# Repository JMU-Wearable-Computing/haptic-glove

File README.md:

# haptic-glove

## Haptic Effect Waveforms

[Image source](https://learn.adafruit.com/assets/72593)

## PCB (Printed Circuit Board)

### Schematic V2.1

### Layout V2.1

#### PCB Edit History
##### V2.0
- Initial board redesign
##### V2.1
- Shifted Arduino placement down 1 mm to allow for more clearance between the Arduino and the motor header pins
- Added graphic to denote onboard IMU directions
- Added a spot on the back of the board to write the board's device ID
- Shifted some silkscreen placements so that part names are not cut off by pads
- Added text to denote correct Arduino orientation
  
## Eagle PCB Set-Up

### OSHPark Plugin
The OSHPark Eagle plugin includes OSHPark design rules and allows the user to send the .brd file directly to an OSHPark cart. See the [OSHPark-Eagle-Tools GitHub](https://github.com/OSHPark/OSHPark-Eagle-Tools)

### Libraries
Included in the repository are:
1. TCA9548APWR.lbr (I2C multiplexer)
2. SparkFun-Eagle-Libraries-main.zip

## Arduino Nano Arduino IDE setup 

### Correct IDE version
Arduino IDE 2.X.X

### Correct board library and name:
#### Board Library
Arduino SAMD Boards (32-bits ARM Cortex-M0+)

#### Board Name
Arduino NANO 33 IoT

### Arduino Libraries
 
1. Adafruit_DRV2605.h
2. Arduino_LSM6DS3.h
3. WiFiNINA.h

### Troubleshooting
Sometimes, Arduino IDE fails to recognize that Nano 33 IoT is connected to a USB port. Should this happen, try the following fixes:
- Attempt to connect it to other USB ports on your machine
- If the above does not work, quickly double click the `RST` button on the Arduino while it is plugged into your machine. This will cause your Arduino's bootloader to run indefinitely. You will know that it has entered this state when you see the onboard LED slowly pulsing on and off. Arduino IDE should now recognize it and you should now be able to upload code.

If neither of these options work, then it is likely that either

(A). the bootloader on the Arduino is missing or corrupted, or  
(B). there is some hardware damage on the Arduino.

Sources: [Forum post 1](https://forum.arduino.cc/t/solved-arduino-nano-33-iot-not-recognized-by-windows-10/621376) & [Forum post 2](https://forum.arduino.cc/t/arduino-nano-33-iot-not-recognized-by-pc/1192703/4)

## Communicating with Nano 33 IoT

Nano 33 IoT can be communicated with via TCP socket connection.
Network credentials can be modified with the `ssid` and `password` variables within the Arduino code.
When booted, the Nano 33 IoT establishes a user definable static IP.

### Onboard LED state meanings
|State|Meaning|
--- | --- |
|OFF|Not connected to network|
|ON|Connected to user specified network|

### Message format
Messages follows the format: `X,n01,n02,n03,n04,n05,n06,n07,n08`

**NOTE FOR SERIAL COMMUNICATION ONLY:** Despite the known issue with [the dastardly eighth motor driver](#the-dastardly-eighth-motor-driver), the message format remains the same. Even if you are not using all eight drivers in your application with Serial communication, values for all eight drivers should be passed if you are sending an [effect message](#effect-messages) unless you are sending an [all stop message](#all-stop-message).

X is a char that signifies the message type. nXX is a number.
Negative numbers will be ignored and the playback of the current haptic effect will continue.
0 will stop the corresponding driver.
All decimals will be rounded DOWN.
Each segment of the message correspondes to the strength of a specific haptic driver, where n01 controls driver 1, n02 controls driver 2, and so on.

#### Effect Messages
For messages of type 'E', numbers [1, 123] will set the playback effect of the corresponding driver.
Numbers higher than 123 will set the playback effect to effect # 123.

##### All Stop Message
Should you want to halt the haptic playback of all drivers, simply passing `'E'` as the entire effect message will do this.

##### Example
The message `'E',100,43,55,1,123,34,99,2` will cause driver one to activate using haptic effect # 100, driver two to activate using haptic effect # 43, and so on. Passing the message `'E',0,-1,100.7,9999,0,0,0,0` afterwards will stop drivers 1, 5, 6, 7, and 8. Driver 2 will remain activated with the same haptic effect as before (# 43), driver 3 will activate using haptic effect # 100, and driver 4 will activate using haptic effect # 123.

#### Acceleration Messages
For messages of type 'A', numbers are used to toggle the continuous collection of acceleration data. Only one number should be passed. Passing the number zero will halt data collection, while any other number will resume data collection. For simplicity's sake, it is recommended to only use the number one to resume data collection. Once started, data will be continuously returned and sent to the client until another acceleration message is recieved that instructs the system to halt data collection.

##### Example
The message `'A',1` will begin continuous acceleration data collection and sending. The message `'A',0` will halt all acceleration data collection and sending.

## Tutorials
### Arduino IDE setup
This will teach you how to set up the Arduino IDE for use of the haptic glove. Prior to following this tutorial, you should already have the Arduino IDE downloaded.

1. Open `firmware-V2.ino`. `network_cred.h` should automatically open in a separate tab
2. Click the `network_cred.h` tab at the top and input your WiFi credentials. Press <kbd>Command</kbd> + <kbd>S</kbd> to save your edits on a Mac (<kbd>Control</kbd> + <kbd>S</kbd> on Windows).
3. Open the Boards Manager by clicking the correct icon on the left of the IDE. Search for `nano 33 iot`. The one board library that should be shown is `Arduino SAMD Boards (32-bits ARM Cortex-M0+)`. Install this library. Feel free to install a newer version than what is shown in the picture.

4. Open the Library manager by clicking the correct icon on the left of the IDE. Search for and install `Adafruit DRV2605 Library`, `Arduino_LSM6DS3` and `WiFiNINA`. Feel free to install newer versions than what are shown in the pictures.

5. Navigate to `Tools`>`Board`>`Arduino`>`SAMD Boards (32-bits ARM Cortex-M0+)` and select `Arduino Nano 33 IoT` as the board.
6. Congratulations! Arduino IDE is now set up to be used with the haptic glove.

### Communicating with the Arduino via serial port
This will teach you how to send messages to the Arduino via the Serial port that will control the haptic motor drivers and the onboard IMU.

#### Initial Arduino set up
1. Complete the [Arduino IDE setup tutorial](#arduino-ide-setup).
2. Set the user-definable variables in the firmware. The value of the variable `DEVICE_ID` does not matter when using serial communication.

**NOTE:** See the [Known Issues section](#known-issues) for an explanation of `theDastardlyEighthDriver`

3. Ensure that the Serial Monitor baud rate is set to 9600

4. Connect the Arduino to your computer via USB, ensure the correct board and port are selected in the Arduino IDE, and upload the firmware by clicking the arrow button in the top left of the IDE.

#### Example Use
We will use an example message that was used in the [Message Format section](#message-format). Feel free to use other example messages from that section to familiarize yourself with the message structure. Or, be brave and create your own message (just be sure to follow the correct structure!)

##### Turning all drivers on with an effect message
1. In the serial monitor, type the following message and then press <kbd>Enter</kbd> (enter it EXACTLY as it appears here): `E,100,43,55,1,123,34,99,2`

2. If the variable `debug` is set to `true`, the following should be the last of what prints to the Serial Monitor:

3. All drivers should now be activated. Driver number 1 should be set to haptic effect # 100, driver number 2 should be set to haptic effect # 43, and so on.

##### Accessing the accelerometer data using an acceleration message
1. In the serial monitor, type the following message and then press <kbd>Enter</kbd> (enter it EXACTLY as it appears here): `A,1`

2. As long as the variable `debug` is set to `true`, the following should print to the Serial Monitor. `outMsg` is the object that is sent to the TCP client. Acceleration data is now being continuously collected.

3. Now input the message `A,0` or just simply `A` into the Serial Monitor. Notice how the continuous collection of accelerometer data has stopped.

### Communicating with the Arduino via TCP socket connection
This will teach you how to send messages to the Arduino via a TCP socket to control the haptic motor drivers and the onboard IMU.

#### Initial Arduino set up
1. Complete the [Arduino IDE setup tutorial](#arduino-ide-setup).
2. Set the user-definable variables in the firmware. Be sure to set `DEVICE_ID` to a unique integer [10, 100].

3. Connect the Arduino to your computer via USB, ensure the correct board and port are selected in the Arduino IDE, and upload the firmware by clicking the arrow button in the top left of the IDE.
4. Once uploaded, you can safely unplug the Arduino from your computer. Congratulations! Your Arduino now has the necessary software and is ready for use with the haptic glove.

#### Setting up Python
This assumes that you already have Python installed and can successfully run a Python script.
1. Clone this repository (glove-V2) to your local computer
2. Open the repository in your preferred IDE (PyCharm is recommended)
3. Congrats! Python is now ready for use with the haptic glove.

#### Example Use
We will use `glove-demo-single.py` for this example. This is meant as a demonstration of the glove-V2 capabilities so that you can go on and create your own applications using the same methods.

1. After cloning this repository, open `glove-demo-single.py`
2. Ensure the correct parameters are set for the Glove object (`device_id`, `port`, `acceleration`, and `verbose`). Explanations for these parameters are in this Python file
3. The demo script is now ready for use. You can go ahead and run it, or customize the effect numbers that are sent to the glove.

**NOTE:** If you choose to activate the accelerometer on the Arduino (this is the default) then be sure that the `acceleration` property of the glove object is set to `True`. This will turn on continuous transmission of acceleration data until the Python script ends. Be sure that `glove.accel_loop` is set to `False` at the end of this example script. Otherwise, the program will be stuck in a loop and will continue to output acceleration data until the program is manually killed.

## Known Issues
### The Dastardly Eighth Motor Driver
#### Explanation and Recommendation
If you are attempting to control the motor drivers via TCP socket connection, attempting to activate the eighth driver (including if you tell it to halt effect playback by passing a zero in the correct place in an [effect message](#effect-messages) when it is already not activated) will cause the WiFi to disconnect. This will prevent reconnection until the onboard WiFi chip is fully turned off/on again by calling `WiFi.end()` and then the custom `WiFiConnect()` function that performs all of the initial WiFi connection procedures. Because of the nature of TCP socket connections, this requires the Arduino and desktop computer to restart their connection and create a new socket and client, at which point the problem will (99 times out of 100) happen again. To remedy this, the boolean variable `theDastardlyEighthDriver` has been added to the firmware that controls the use of the eighth driver. If you are at all using TCP socket connections with the haptic glove, be sure to keep this variable set to `false` so that the WiFi disconnect problem does not occur. You will only be able to use seven of the eight drivers, but the WiFi connection will be reliable and shouldn't drop. If you are strictly using Serial communication to control the motor drivers, then feel free to set `theDastardlyEighthDriver` to `true`. This will allow you to use all eight drivers for your application.
#### Potential Cause
The current theory for why this issue is happening is that the moment the I2C multiplexer begins to communicate with this eighth driver, since the driver's I2C lines are tied high and the mux pulls them low to communicate, power and ground are very briefly shorted. It is believed that this short then messes with the WiFi chip's power supply, causing WiFi to drop and requiring the WiFi chip to be reset.

This issue is present on all of the existing haptic glove V2.0 boards, so it is not believed that it is simply an issue with the soldering of the components, however this is still a possibility. However, it may be a tolerance issue with the traces on the PCB itself. As of now (May 2024), no V2.1 boards have been fabricated so it is unknown if this issue is present on those (although it is likely that it is). Also, it is worth noting that during fabrication of the PCBs there was a power-ground short somewhere that disappeared before we could track down the cause. It disappeared once all components were soldered onto the PCB. This may be related to the problem explained above, although there is no corroborating evidence to prove that this is the case.

The true cause of this issue is unknown, so it is best to utilize the `theDastardlyEighthDriver` variable to only use seven drivers if your application uses TCP sockets.

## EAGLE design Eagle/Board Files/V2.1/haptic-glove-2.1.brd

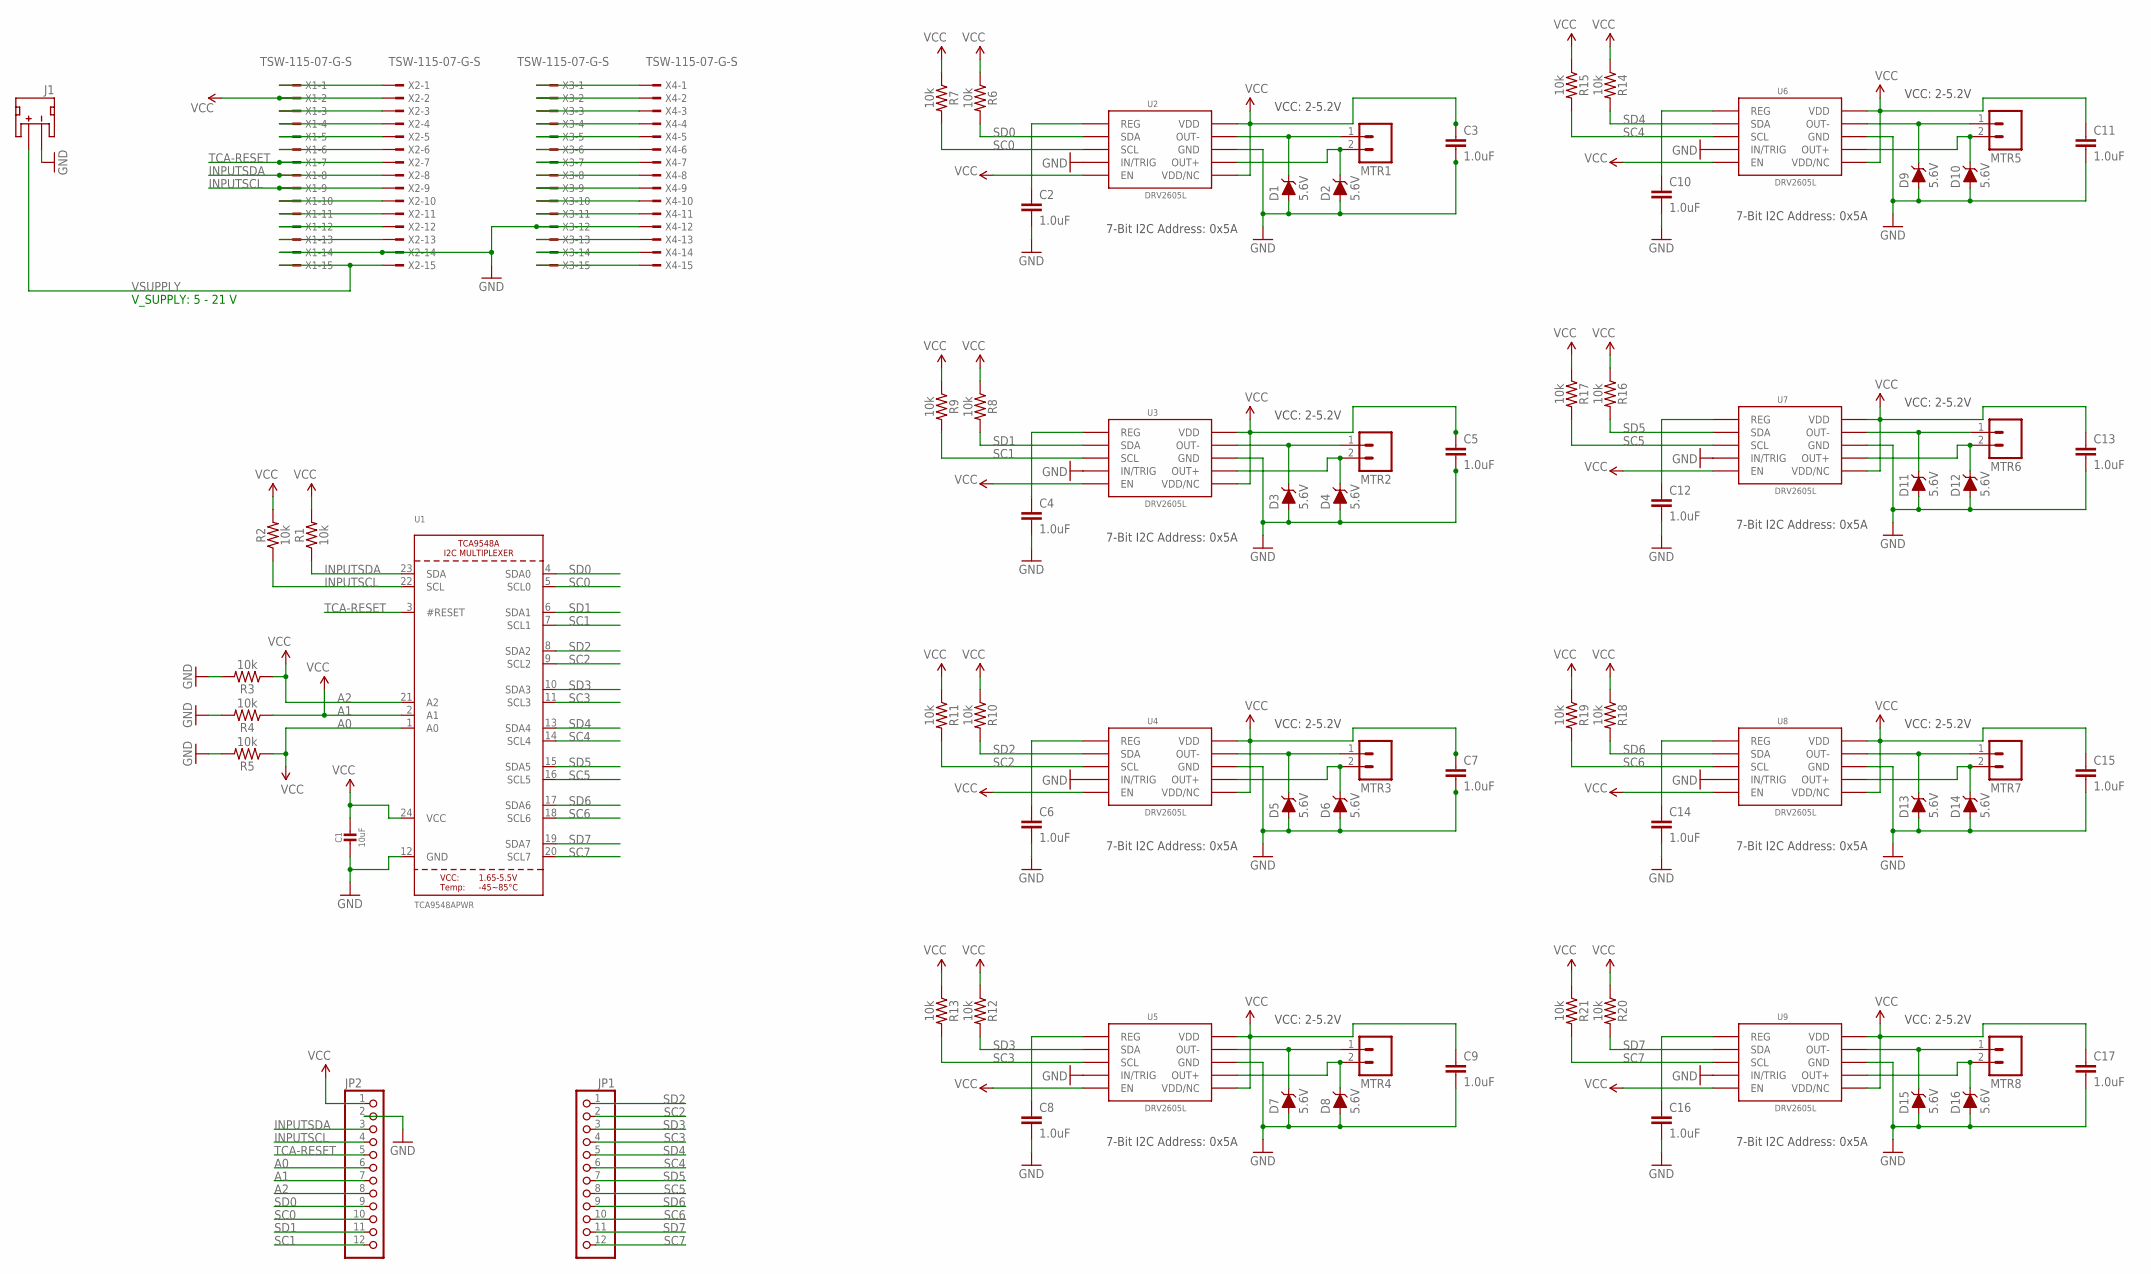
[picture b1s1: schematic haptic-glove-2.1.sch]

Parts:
C1: 10uF; 0805-NO
C2, C3, C4, C5, C6, C7, C8, C9, C10, C11, C12, C13, C14, C15, C16, C17: 1.0uF; 0402-CAP; MPN GRM155R61E105KA12D
D1, D2, D3, D4, D5, D6, D7, D8, D9, D10, D11, D12, D13, D14, D15, D16: 5.6V; SOD-323
J1: JST_2MM_MALE; JST-2-SMD
JP1, JP2: HEADER-1X12; 1X12_ROUND
MTR1, MTR2, MTR3, MTR4, MTR5, MTR6, MTR7, MTR8: M02PTH; 1X02@1
R1, R2, R3, R4, R5, R6, R7, R8, R9, R10, R11, R12, R13, R14, R15, R16, R17, R18, R19, R20, R21: 10k; 0603
U1: TCA9548APWR; TSSOP24
U2, U3, U4, U5, U6, U7, U8, U9: DRV2605L; VSSOP-10
X1, X2, X3, X4: TSW-115-07-G-S; TSW-115-XX-G-S

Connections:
A0: JP2.6, R5.1, U1.1 (A0)
A1: JP2.7, R4.1, U1.2 (A1)
A2: JP2.8, R3.1, U1.21 (A2)
EN1: X3.2, X4.2
EN2: X3.4, X4.4
EN3: X3.8, X4.8
EN4: X3.11, X4.11
GND: C1.2, C2.2, C3.2, C4.2, C5.2, C6.2, C7.2, C8.2, C9.2, C10.2, C11.2, C12.2, C13.2, C14.2, C15.2, C16.2, C17.2, D1.A, D2.A, D3.A, D4.A, D5.A, D6.A, D7.A, D8.A, D9.A, D10.A, D11.A, D12.A, D13.A, D14.A, D15.A, D16.A, J1.1 (-), JP2.2, R3.2, R4.2, R5.2, U1.12 (GND), U2.P$4 (IN/TRIG), U2.P$8 (GND), U3.P$4 (IN/TRIG), U3.P$8 (GND), U4.P$4 (IN/TRIG), U4.P$8 (GND), U5.P$4 (IN/TRIG), U5.P$8 (GND), U6.P$4 (IN/TRIG), U6.P$8 (GND), U7.P$4 (IN/TRIG), U7.P$8 (GND), U8.P$4 (IN/TRIG), U8.P$8 (GND), U9.P$4 (IN/TRIG), U9.P$8 (GND), X1.14, X2.14, X3.12, X4.12
IN/TRIG1: X3.1, X4.1
IN/TRIG2: X3.3, X4.3
IN/TRIG3: X3.7, X4.7
IN/TRIG4: X3.10, X4.10
IN/TRIG5: X1.6, X2.6
INPUTSCL: JP2.4, R2.1, U1.22 (SCL), X1.9, X2.9
INPUTSDA: JP2.3, R1.1, U1.23 (SDA), X1.8, X2.8
unnamed: C4.1, U3.P$1 (REG)
unnamed: C10.1, U6.P$1 (REG)
unnamed: D9.C, MTR5.1, U6.P$9 (OUT-)
unnamed: D3.C, MTR2.1, U3.P$9 (OUT-)
unnamed: D4.C, MTR2.2, U3.P$7 (OUT+)
unnamed: C8.1, U5.P$1 (REG)
unnamed: D10.C, MTR5.2, U6.P$7 (OUT+)
unnamed: X1.1, X2.1
unnamed: D7.C, MTR4.1, U5.P$9 (OUT-)
unnamed: D8.C, MTR4.2, U5.P$7 (OUT+)
unnamed: C6.1, U4.P$1 (REG)
unnamed: X1.3, X2.3
unnamed: D5.C, MTR3.1, U4.P$9 (OUT-)
unnamed: D6.C, MTR3.2, U4.P$7 (OUT+)
unnamed: C12.1, U7.P$1 (REG)
unnamed: X1.4, X2.4
unnamed: D11.C, MTR6.1, U7.P$9 (OUT-)
unnamed: D12.C, MTR6.2, U7.P$7 (OUT+)
unnamed: C14.1, U8.P$1 (REG)
unnamed: X1.5, X2.5
unnamed: D13.C, MTR7.1, U8.P$9 (OUT-)
unnamed: D14.C, MTR7.2, U8.P$7 (OUT+)
unnamed: C16.1, U9.P$1 (REG)
unnamed: D15.C, MTR8.1, U9.P$9 (OUT-)
unnamed: D16.C, MTR8.2, U9.P$7 (OUT+)
unnamed: C2.1, U2.P$1 (REG)
unnamed: X1.10, X2.10
unnamed: X1.11, X2.11
unnamed: D1.C, MTR1.1, U2.P$9 (OUT-)
unnamed: D2.C, MTR1.2, U2.P$7 (OUT+)
unnamed: X1.12, X2.12
unnamed: X1.13, X2.13
unnamed: X3.5, X4.5
unnamed: X3.6, X4.6
unnamed: X3.9, X4.9
unnamed: X3.13, X4.13
unnamed: X3.14, X4.14
unnamed: X3.15, X4.15
SC0: JP2.10, R7.2, U1.5 (SCL0), U2.P$2 (SCL)
SC1: JP2.12, R9.2, U1.7 (SCL1), U3.P$2 (SCL)
SC2: JP1.2, R11.2, U1.9 (SCL2), U4.P$2 (SCL)
SC3: JP1.4, R13.2, U1.11 (SCL3), U5.P$2 (SCL)
SC4: JP1.6, R15.2, U1.14 (SCL4), U6.P$2 (SCL)
SC5: JP1.8, R17.2, U1.16 (SCL5), U7.P$2 (SCL)
SC6: JP1.10, R19.2, U1.18 (SCL6), U8.P$2 (SCL)
SC7: JP1.12, R21.2, U1.20 (SCL7), U9.P$2 (SCL)
SD0: JP2.9, R6.2, U1.4 (SDA0), U2.P$3 (SDA)
SD1: JP2.11, R8.2, U1.6 (SDA1), U3.P$3 (SDA)
SD2: JP1.1, R10.2, U1.8 (SDA2), U4.P$3 (SDA)
SD3: JP1.3, R12.2, U1.10 (SDA3), U5.P$3 (SDA)
SD4: JP1.5, R14.2, U1.13 (SDA4), U6.P$3 (SDA)
SD5: JP1.7, R16.2, U1.15 (SDA5), U7.P$3 (SDA)
SD6: JP1.9, R18.2, U1.17 (SDA6), U8.P$3 (SDA)
SD7: JP1.11, R20.2, U1.19 (SDA7), U9.P$3 (SDA)
TCA-RESET: JP2.5, U1.3 (#RESET), X1.7, X2.7
VCC: C1.1, C3.1, C5.1, C7.1, C9.1, C11.1, C13.1, C15.1, C17.1, JP2.1, R1.2, R2.2, R6.1, R7.1, R8.1, R9.1, R10.1, R11.1, R12.1, R13.1, R14.1, R15.1, R16.1, R17.1, R18.1, R19.1, R20.1, R21.1, U1.24 (VCC), U2.P$5 (EN), U2.P$6 (VDD/NC), U2.P$10 (VDD), U3.P$5 (EN), U3.P$6 (VDD/NC), U3.P$10 (VDD), U4.P$5 (EN), U4.P$6 (VDD/NC), U4.P$10 (VDD), U5.P$5 (EN), U5.P$6 (VDD/NC), U5.P$10 (VDD), U6.P$5 (EN), U6.P$6 (VDD/NC), U6.P$10 (VDD), U7.P$5 (EN), U7.P$6 (VDD/NC), U7.P$10 (VDD), U8.P$5 (EN), U8.P$6 (VDD/NC), U8.P$10 (VDD), U9.P$5 (EN), U9.P$6 (VDD/NC), U9.P$10 (VDD), X1.2, X2.2
VSUPPLY: J1.2 (+), X1.15, X2.15

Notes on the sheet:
7-Bit I2C Address: 0x5A
VCC: 2-5.2V
V_SUPPLY: 5 - 21 V

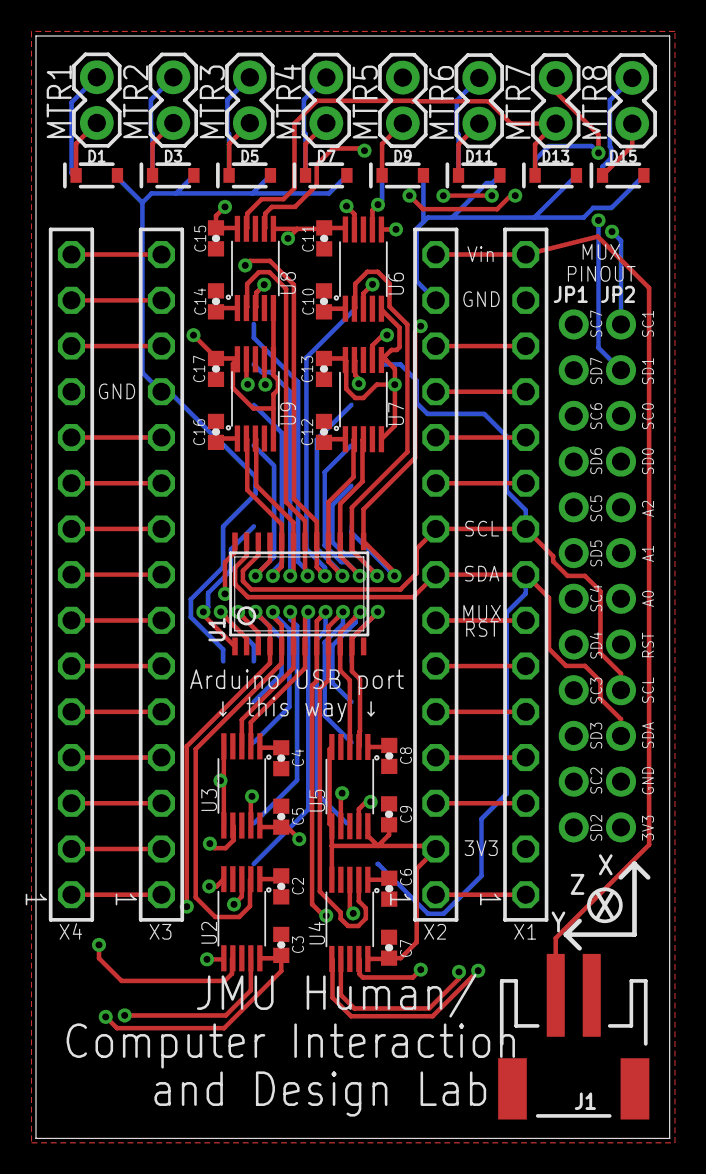
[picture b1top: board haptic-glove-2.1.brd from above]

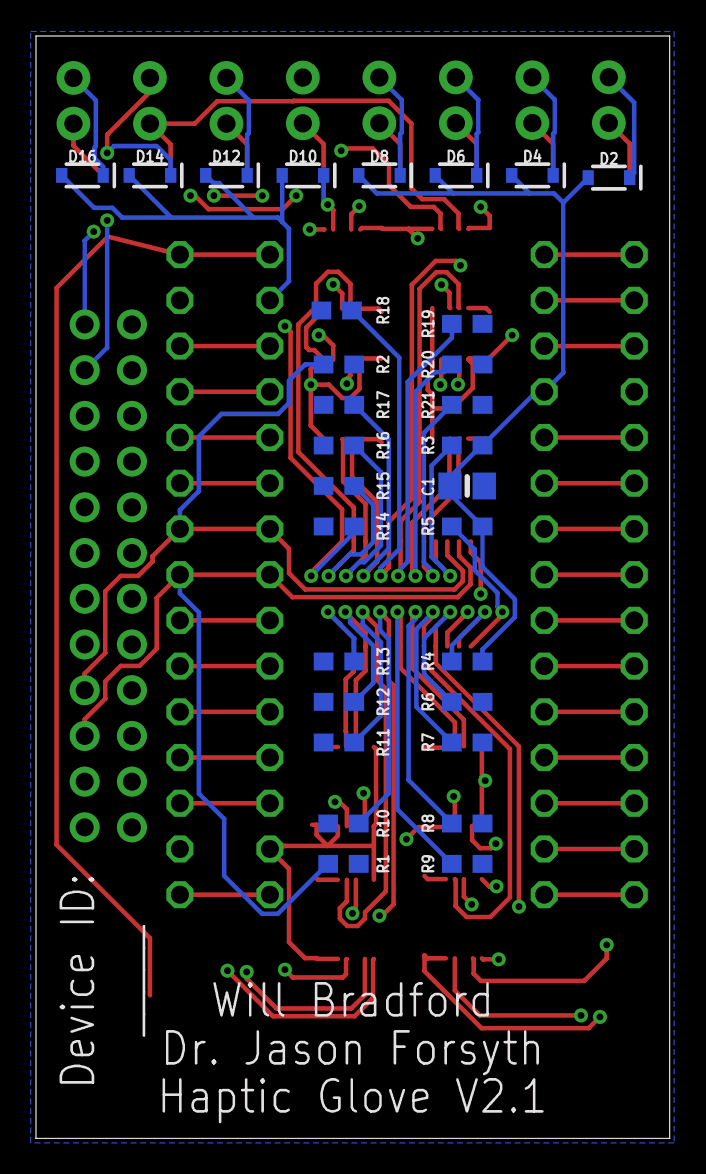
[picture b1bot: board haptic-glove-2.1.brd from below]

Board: 4 copper layers, 35.2 x 61.2 mm, 78 parts (30 on the bottom side), 72 nets.

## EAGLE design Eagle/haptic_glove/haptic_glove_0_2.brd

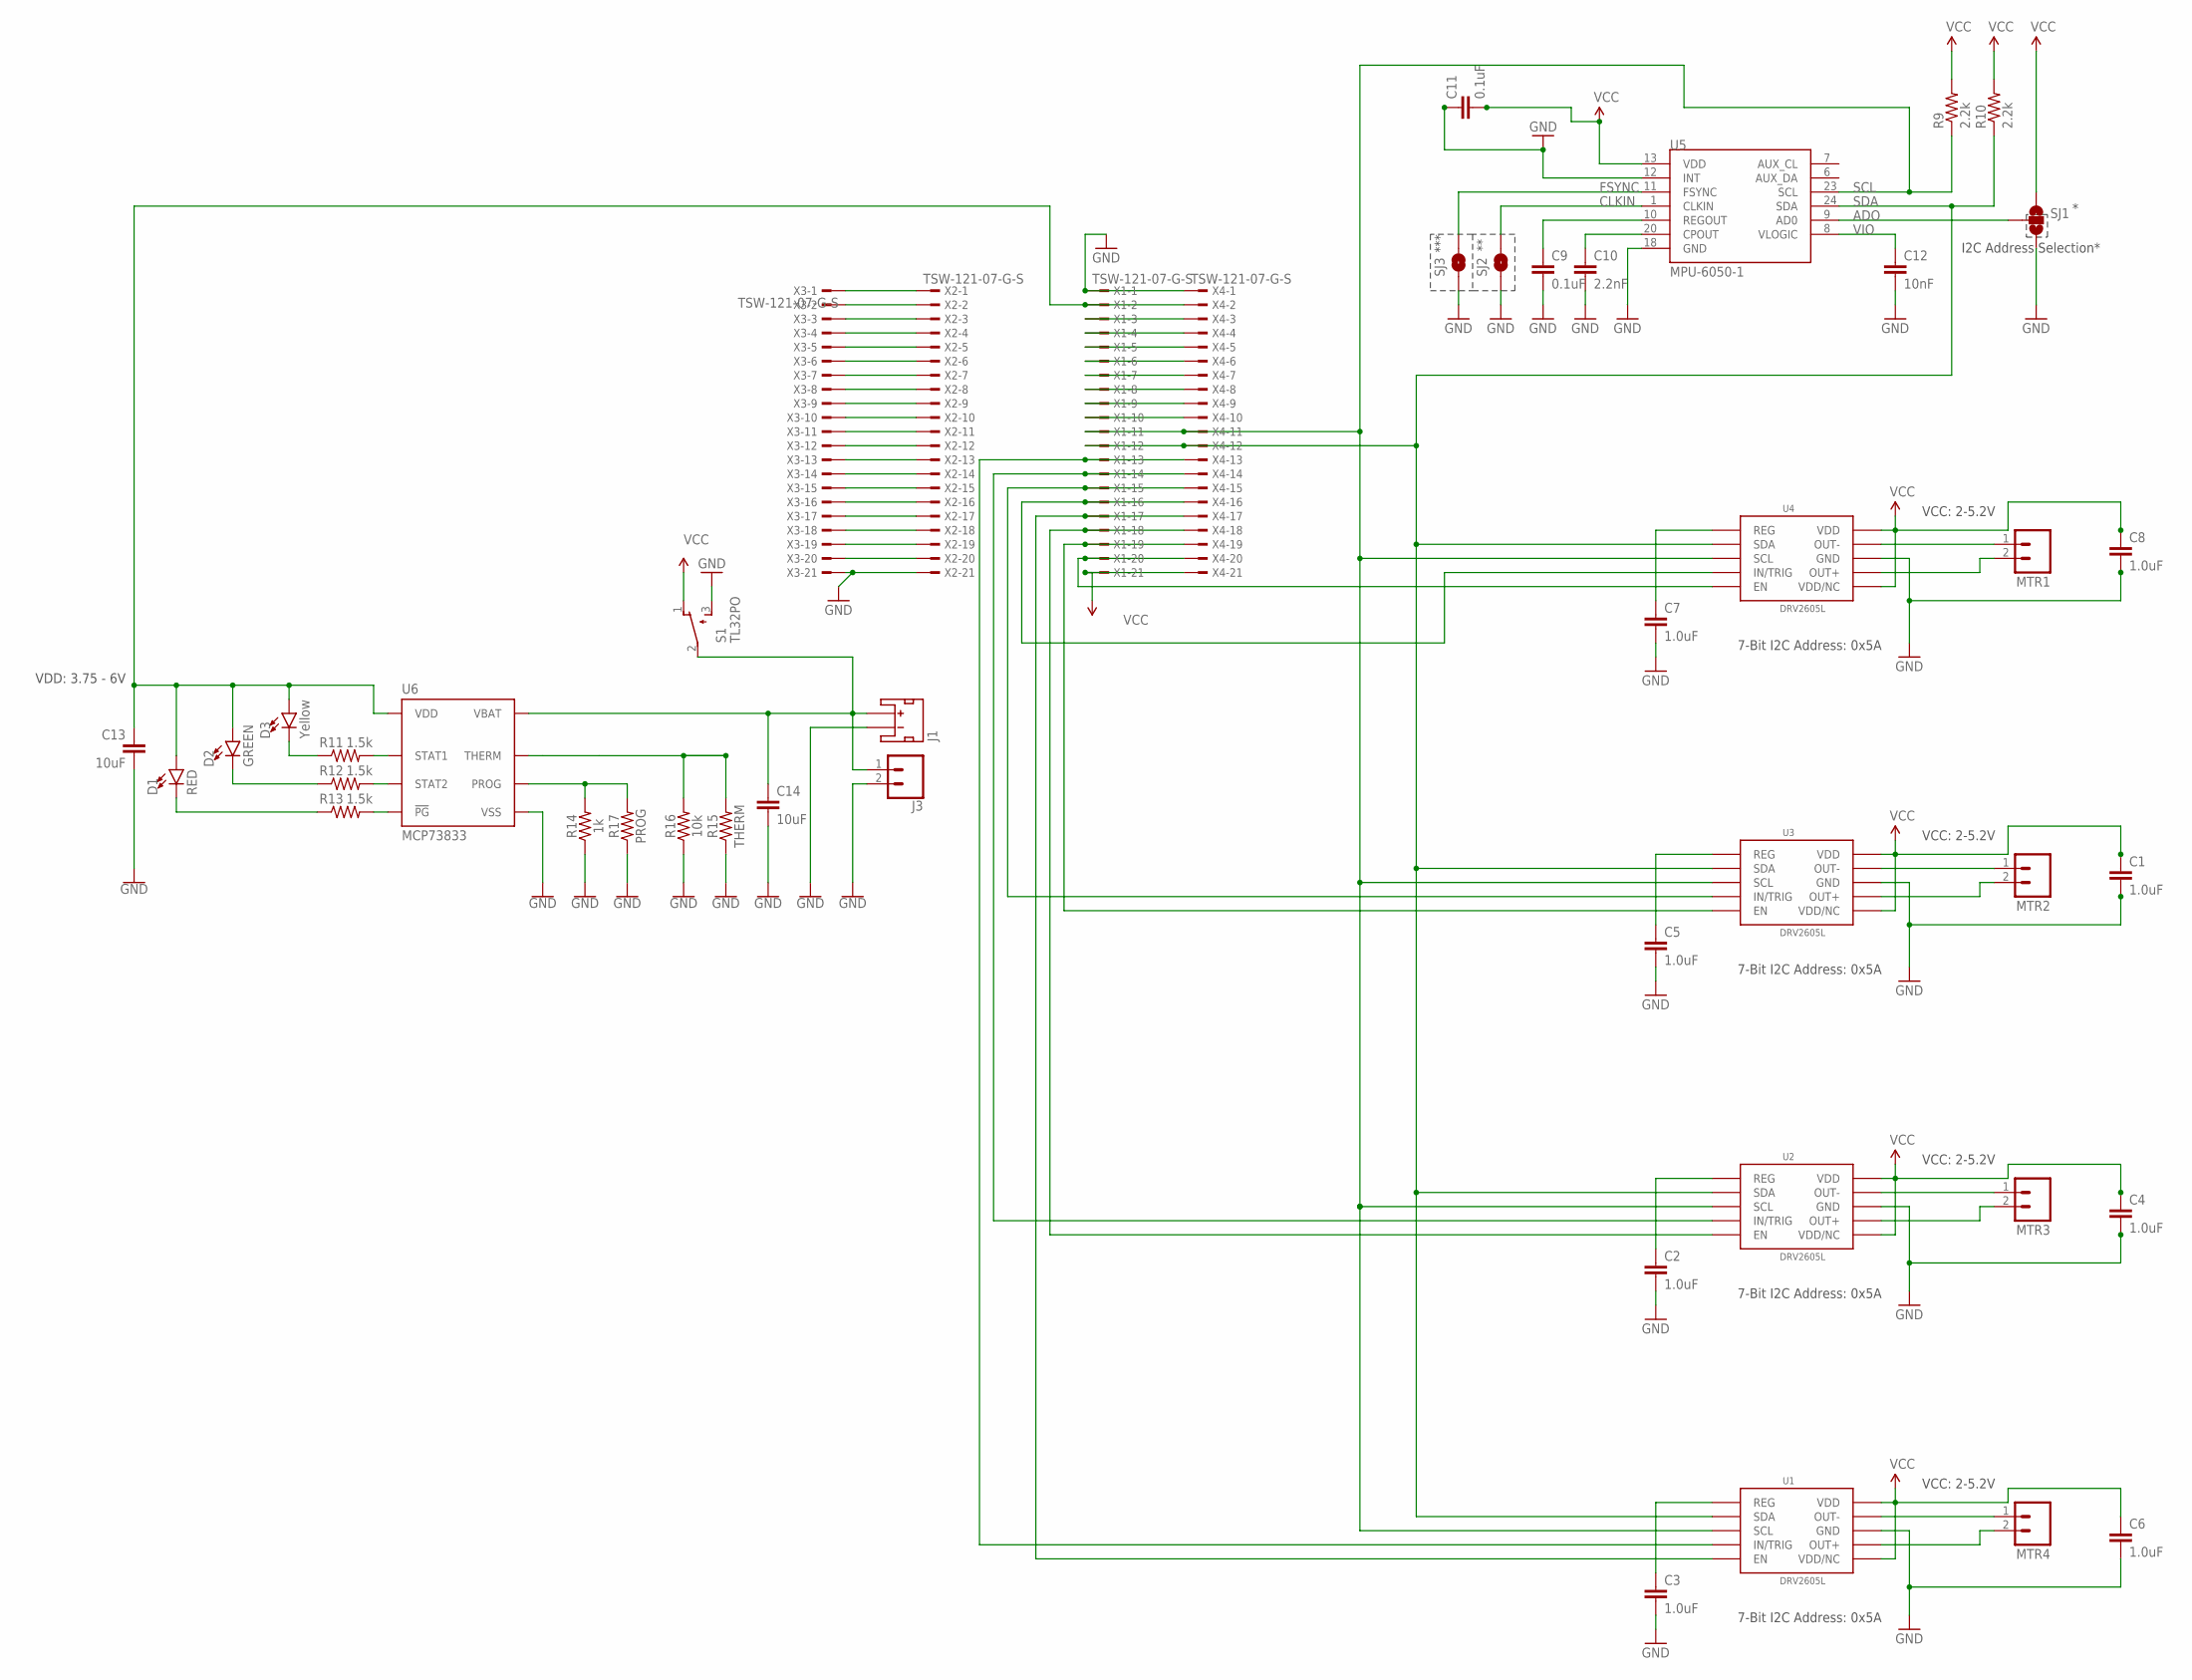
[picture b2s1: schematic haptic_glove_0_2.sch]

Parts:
C1, C2, C3, C4, C5, C6, C7, C8: 1.0uF; 0402-CAP
C9: 0.1uF; 0603-CAP
C10: 2.2nF; 0603-CAP
C11: 0.1uF; 0402-CAP
C12: 10nF; 0603-CAP
C13, C14: 10uF; 0603
D1: RED; LED-0603
D2: GREEN; LED-0603
D3: Yellow; LED-0603
J1: JST_2MM_MALE; JST-2-SMD
J3: CONN_021X02_NO_SILK; 1X02_NO_SILK
MTR1, MTR2, MTR3, MTR4: M02PTH; 1X02@1
R9, R10: 2.2k; 0603-RES
R11, R12, R13: 1.5k; 0603
R14: 1k; 0603
R15: THERM; AXIAL-0.3
R16: 10k; 0603
R17: PROG; AXIAL-0.3
S1: TL32PO; TL3XPO
SJ1: SOLDERJUMPER_2WAYPASTE2&3; SJ_3_PASTE2&3
SJ2, SJ3: SOLDERJUMPERTRACE; SJ_2S-TRACE
U1, U2, U3, U4: DRV2605L; VSSOP-10
U5: MPU-6050-1; QFN-24-4MM2
U6: MCP73833; DFN-10
X1, X2, X3, X4: TSW-121-07-G-S; TSW-121-XX-G-S

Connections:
ADO: SJ1.2, U5.9 (AD0)
CLKIN: SJ2.2, U5.1 (CLKIN)
FSYNC: SJ3.2, U5.11 (FSYNC)
GND: C1.2, C2.2, C3.2, C4.2, C5.2, C6.2, C7.2, C8.2, C9.2, C10.2, C11.1, C12.2, C13.2, C14.2, J1.1 (-), J3.2, R14.1, R15.P$1 (1), R16.1, R17.P$1 (1), S1.3 (S), SJ1.3, SJ2.1, SJ3.1, U1.P$8 (GND), U2.P$8 (GND), U3.P$8 (GND), U4.P$8 (GND), U5.12 (INT), U5.18 (GND), U6.P$5 (VSS), U6.P$11 (VSS), X1.1, X2.21, X3.21, X4.1
unnamed: X2.1, X3.1
unnamed: X2.2, X3.2
unnamed: C3.1, U1.P$1 (REG)
unnamed: U1.P$4 (IN/TRIG), X1.13, X4.13
unnamed: U1.P$5 (EN), X1.17, X4.17
unnamed: MTR4.1, U1.P$9 (OUT-)
unnamed: MTR4.2, U1.P$7 (OUT+)
unnamed: C2.1, U2.P$1 (REG)
unnamed: U2.P$4 (IN/TRIG), X1.14, X4.14
unnamed: U2.P$5 (EN), X1.18, X4.18
unnamed: MTR3.1, U2.P$9 (OUT-)
unnamed: MTR3.2, U2.P$7 (OUT+)
unnamed: X2.3, X3.3
unnamed: X2.4, X3.4
unnamed: C5.1, U3.P$1 (REG)
unnamed: U3.P$4 (IN/TRIG), X1.15, X4.15
unnamed: U3.P$5 (EN), X1.19, X4.19
unnamed: MTR2.1, U3.P$9 (OUT-)
unnamed: MTR2.2, U3.P$7 (OUT+)
unnamed: X2.5, X3.5
unnamed: X2.6, X3.6
unnamed: C7.1, U4.P$1 (REG)
unnamed: U4.P$4 (IN/TRIG), X1.16, X4.16
unnamed: U4.P$5 (EN), X1.20, X4.20
unnamed: MTR1.1, U4.P$9 (OUT-)
unnamed: MTR1.2, U4.P$7 (OUT+)
unnamed: X2.7, X3.7
unnamed: X2.8, X3.8
unnamed: C10.1, U5.20 (CPOUT)
unnamed: C9.1, U5.10 (REGOUT)
unnamed: X2.9, X3.9
unnamed: X2.10, X3.10
unnamed: X2.11, X3.11
unnamed: X2.12, X3.12
unnamed: X2.13, X3.13
unnamed: X2.14, X3.14
unnamed: X2.15, X3.15
unnamed: X2.16, X3.16
unnamed: X2.17, X3.17
unnamed: X2.18, X3.18
unnamed: X2.19, X3.19
unnamed: X2.20, X3.20
unnamed: C14.1, J1.2 (+), J3.1, S1.2, U6.P$9 (VBAT), U6.P$10 (VBAT)
unnamed: X1.10, X4.10
unnamed: X1.9, X4.9
unnamed: X1.8, X4.8
unnamed: X1.7, X4.7
unnamed: X1.6, X4.6
unnamed: X1.5, X4.5
unnamed: X1.4, X4.4
unnamed: X1.3, X4.3
unnamed: C13.1, D1.A, D2.A, D3.A, U6.P$1 (VDD), U6.P$2 (VDD), X1.2, X4.2
unnamed: D1.C, R13.1
unnamed: D2.C, R12.1
unnamed: D3.C, R11.1
PG: R13.2, U6.P$7 (!PG)
PROG: R14.2, R17.P$2 (2), U6.P$6 (PROG)
SCL: R9.1, U1.P$2 (SCL), U2.P$2 (SCL), U3.P$2 (SCL), U4.P$2 (SCL), U5.23 (SCL), X1.11, X4.11
SDA: R10.1, U1.P$3 (SDA), U2.P$3 (SDA), U3.P$3 (SDA), U4.P$3 (SDA), U5.24 (SDA), X1.12, X4.12
STAT1: R11.2, U6.P$3 (STAT1)
STAT2: R12.2, U6.P$4 (STAT2)
THERM: R15.P$2 (2), R16.2, U6.P$8 (THERM)
VCC: C1.1, C4.1, C6.1, C8.1, C11.2, R9.2, R10.2, S1.1 (O), SJ1.1, U1.P$6 (VDD/NC), U1.P$10 (VDD), U2.P$6 (VDD/NC), U2.P$10 (VDD), U3.P$6 (VDD/NC), U3.P$10 (VDD), U4.P$6 (VDD/NC), U4.P$10 (VDD), U5.13 (VDD), X1.21, X4.21
VIO: C12.1, U5.8 (VLOGIC)

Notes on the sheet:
7-Bit I2C Address: 0x5A
VCC: 2-5.2V
I2C Address Selection*
***
VDD: 3.75 - 6V

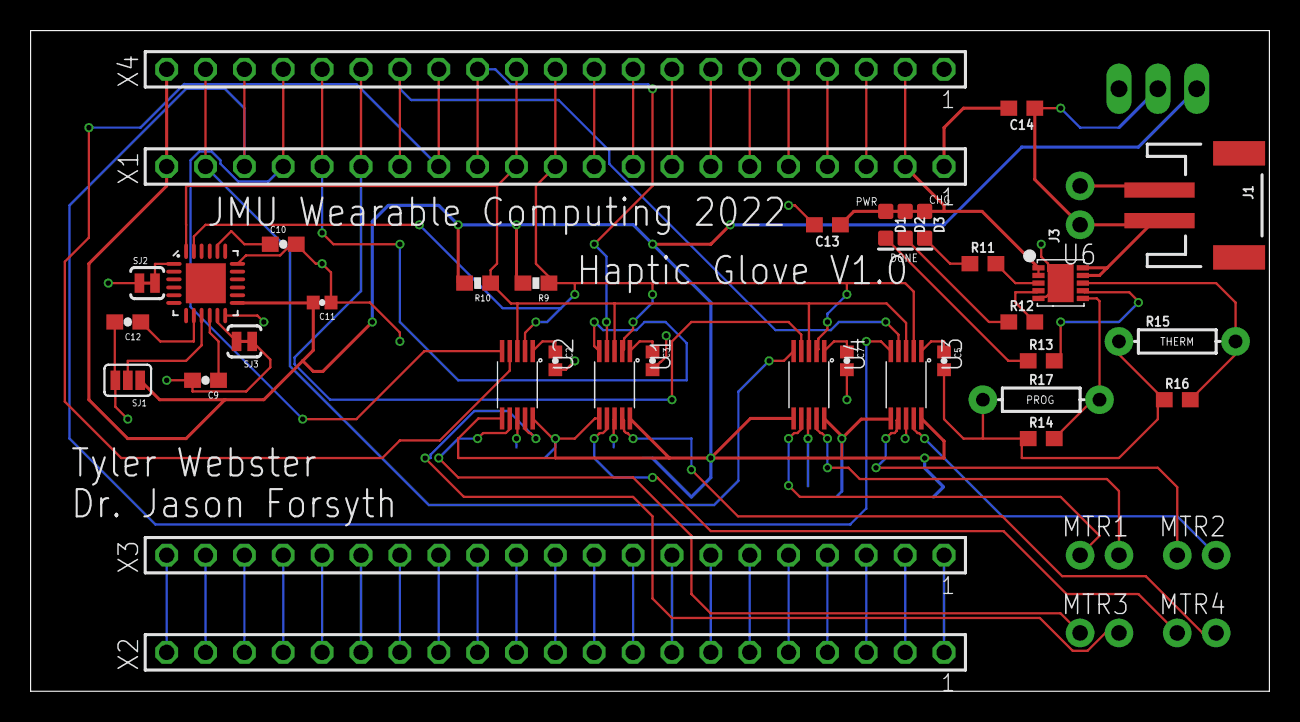
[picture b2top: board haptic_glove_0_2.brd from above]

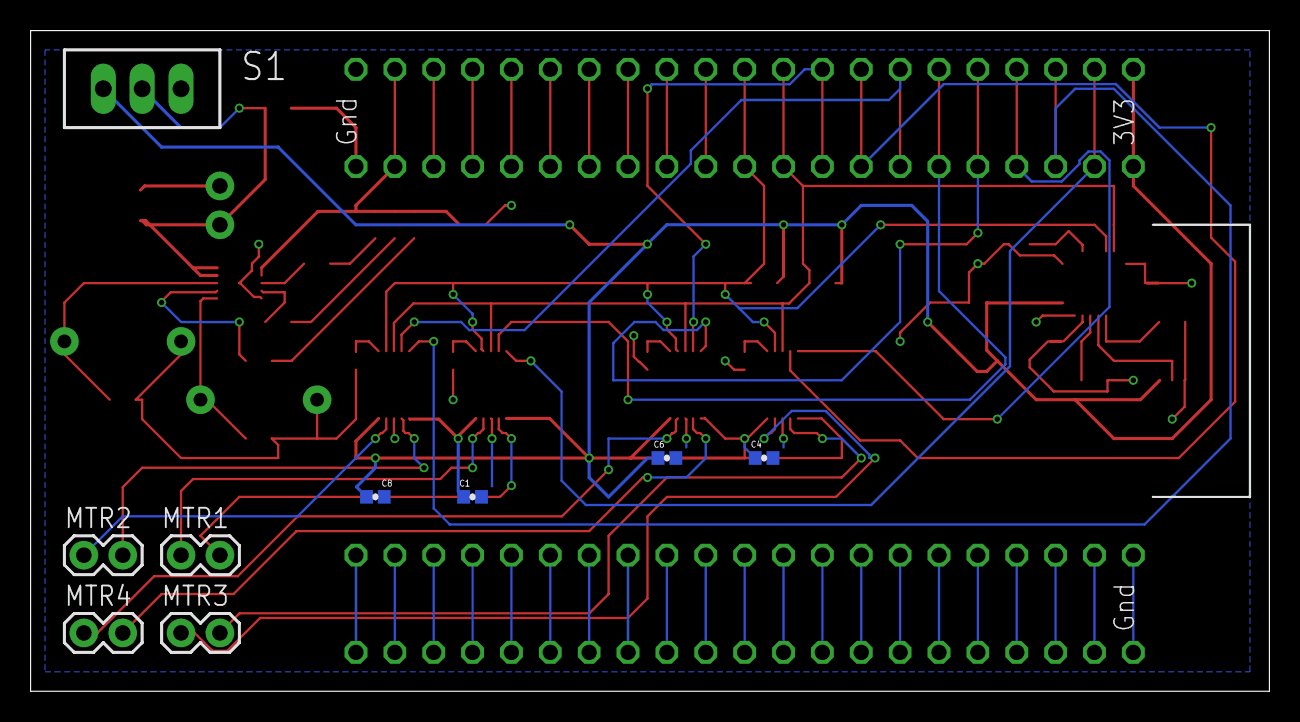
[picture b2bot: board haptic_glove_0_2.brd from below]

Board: 2 copper layers, 81.0 x 43.2 mm, 46 parts (9 on the bottom side), 68 nets.

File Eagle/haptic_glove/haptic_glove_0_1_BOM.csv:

"Part";"Value";"Device";"Package";"Description";"MF";"MPN";"OC_FARNELL";"OC_NEWARK";"POPULARITY";"PROD_ID";"SF_ID";"VALUE";
"C1";"1.0uF";"1.0UF-16V-10%(0402)";"0402-CAP";"";"";"";"";"";"";"CAP-12417";"";"1.0uF";
"C2";"1.0uF";"1.0UF-16V-10%(0402)";"0402-CAP";"";"";"";"";"";"";"CAP-12417";"";"1.0uF";
"C3";"1.0uF";"1.0UF-16V-10%(0402)";"0402-CAP";"";"";"";"";"";"";"CAP-12417";"";"1.0uF";
"C4";"1.0uF";"1.0UF-16V-10%(0402)";"0402-CAP";"";"";"";"";"";"";"CAP-12417";"";"1.0uF";
"C5";"1.0uF";"1.0UF-16V-10%(0402)";"0402-CAP";"";"";"";"";"";"";"CAP-12417";"";"1.0uF";
"C6";"1.0uF";"1.0UF-16V-10%(0402)";"0402-CAP";"";"";"";"";"";"";"CAP-12417";"";"1.0uF";
"C7";"1.0uF";"1.0UF-16V-10%(0402)";"0402-CAP";"";"";"";"";"";"";"CAP-12417";"";"1.0uF";
"C8";"1.0uF";"1.0UF-16V-10%(0402)";"0402-CAP";"";"";"";"";"";"";"CAP-12417";"";"1.0uF";
"C9";"0.1uF";"CAP0603-CAP";"0603-CAP";"Capacitor";"";"";"";"";"";"";"";"";
"C10";"2.2nF";"CAP0603-CAP";"0603-CAP";"Capacitor";"";"";"";"";"";"";"";"";
"C11";"0.1uF";"1.0UF-16V-10%(0402)";"0402-CAP";"";"";"";"";"";"";"CAP-12417";"";"1.0uF";
"C12";"10nF";"CAP0603-CAP";"0603-CAP";"Capacitor";"";"";"";"";"";"";"";"";
"C13";"10uF";"10UF-0603-6.3V-20%";"0603";"10.0µF ceramic capacitors";"";"";"";"";"";"CAP-11015";"";"10uF";
"C14";"10uF";"10UF-0603-6.3V-20%";"0603";"10.0µF ceramic capacitors";"";"";"";"";"";"CAP-11015";"";"10uF";
"D1";"RED";"LED-RED0603";"LED-0603";"Red SMD LED";"";"";"";"";"";"DIO-00819";"";"RED";
"D2";"GREEN";"LED-GREEN0603";"LED-0603";"Green SMD LED";"";"";"";"";"";"DIO-00821";"";"GREEN";
"D3";"Yellow";"LED-YELLOW0603";"LED-0603";"Yellow SMD LED";"";"";"";"";"";"DIO-09003";"";"Yellow";
"J1";"";"JST_2MM_MALE";"JST-2-SMD";"JST 2MM MALE RA CONNECTOR";"";"";"";"";"";"CONN-11443";"PRT-08612";"";
"J3";"";"CONN_021X02_NO_SILK";"1X02_NO_SILK";"Multi connection point. Often used as Generic Header-pin footprint for 0.1 inch spaced/style header connections";"";"";"";"";"";"";"";"";
"MTR1";"";"M02PTH";"1X02@1";"Standard 2-pin 0.1" header. Use with";"";"";"";"";"";"";"";"";
"MTR2";"";"M02PTH";"1X02@1";"Standard 2-pin 0.1" header. Use with";"";"";"";"";"";"";"";"";
"MTR3";"";"M02PTH";"1X02@1";"Standard 2-pin 0.1" header. Use with";"";"";"";"";"";"";"";"";
"MTR4";"";"M02PTH";"1X02@1";"Standard 2-pin 0.1" header. Use with";"";"";"";"";"";"";"";"";
"R9";"2.2k";"RESISTOR0603-RES";"0603-RES";"Resistor";"";"";"";"";"";"";"";"";
"R10";"2.2k";"RESISTOR0603-RES";"0603-RES";"Resistor";"";"";"";"";"";"";"";"";
"R11";"1.5k";"1.5KOHM-0603-1/10W-1%";"0603";"1.5kΩ resistor";"";"";"";"";"";"RES-08306";"";"1.5k";
"R12";"1.5k";"1.5KOHM-0603-1/10W-1%";"0603";"1.5kΩ resistor";"";"";"";"";"";"RES-08306";"";"1.5k";
"R13";"1.5k";"1.5KOHM-0603-1/10W-1%";"0603";"1.5kΩ resistor";"";"";"";"";"";"RES-08306";"";"1.5k";
"R14";"1k";"1KOHM-0603-1/10W-1%";"0603";"1kΩ resistor";"";"";"";"";"";"RES-07856";"";"1k";
"R15";"THERM";"RESISTORAXIAL-0.3";"AXIAL-0.3";"Generic Resistor Package";"";"";"";"";"";" ";"";" ";
"R16";"10k";"10KOHM-0603-1/10W-1%";"0603";"10kΩ resistor";"";"";"";"";"";"RES-00824";"";"10k";
"R17";"PROG";"RESISTORAXIAL-0.3";"AXIAL-0.3";"Generic Resistor Package";"";"";"";"";"";" ";"";" ";
"S1";"TL32PO";"TL32PO";"TL3XPO";"TINY SWITCH ON - MOM";"";"";"";"";"2";"";"";"";
"SJ1";"";"SOLDERJUMPER_2WAYPASTE2&3";"SJ_3_PASTE2&3";"Solder Jumper";"";"";"";"";"";"";"";"";
"SJ2";"";"SOLDERJUMPERTRACE";"SJ_2S-TRACE";"Solder Jumper";"";"";"";"";"";"";"";"";
"SJ3";"";"SOLDERJUMPERTRACE";"SJ_2S-TRACE";"Solder Jumper";"";"";"";"";"";"";"";"";
"U1";"DRV2605L";"DRV2605L";"VSSOP-10";"";"";"";"";"";"";"IC-13504";"";"";
"U2";"DRV2605L";"DRV2605L";"VSSOP-10";"";"";"";"";"";"";"IC-13504";"";"";
"U3";"DRV2605L";"DRV2605L";"VSSOP-10";"";"";"";"";"";"";"IC-13504";"";"";
"U4";"DRV2605L";"DRV2605L";"VSSOP-10";"";"";"";"";"";"";"IC-13504";"";"";
"U5";"MPU-6050-1";"MPU-6050-1";"QFN-24-4MM2";"";"";"";"";"";"";"";"";"";
"U6";"MCP73833";"MCP73833";"DFN-10";"";"";"";"";"";"";"IC-14369";"";"MCP73833";
"X1";"TSW-121-07-G-S";"TSW-121-07-G-S";"TSW-121-XX-G-S";"THROUGH-HOLE .025" SQ POST HEADER";"Samtec Inc.";"TSW-121-07-G-S";"";"";"";"";"";"";
"X2";"TSW-121-07-G-S";"TSW-121-07-G-S";"TSW-121-XX-G-S";"THROUGH-HOLE .025" SQ POST HEADER";"Samtec Inc.";"TSW-121-07-G-S";"";"";"";"";"";"";
"X3";"TSW-121-07-G-S";"TSW-121-07-G-S";"TSW-121-XX-G-S";"THROUGH-HOLE .025" SQ POST HEADER";"Samtec Inc.";"TSW-121-07-G-S";"";"";"";"";"";"";
"X4";"TSW-121-07-G-S";"TSW-121-07-G-S";"TSW-121-XX-G-S";"THROUGH-HOLE .025" SQ POST HEADER";"Samtec Inc.";"TSW-121-07-G-S";"";"";"";"";"";"";

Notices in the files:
parts and their libraries:
SparkFun-Capacitors: Licensing: Creative Commons ShareAlike 4.0 International - https://creativecommons.org/licenses/by-sa/4.0
SparkFun-Connectors: Licensing: CC v3.0 Share-Alike You are welcome to use this library for commercial purposes.
